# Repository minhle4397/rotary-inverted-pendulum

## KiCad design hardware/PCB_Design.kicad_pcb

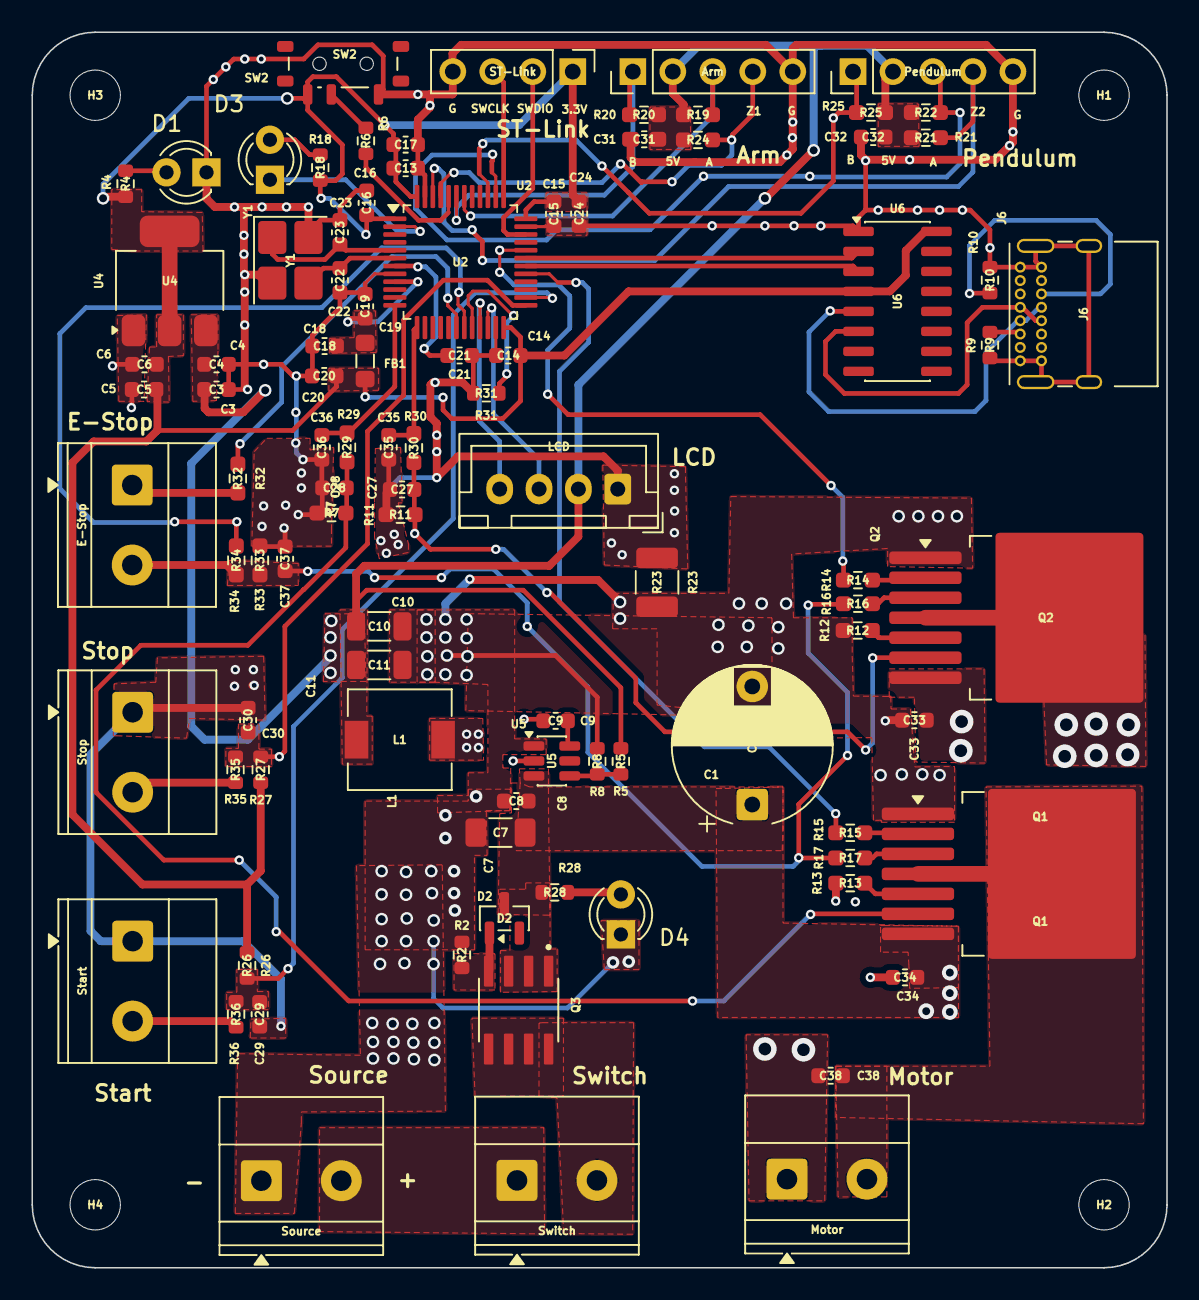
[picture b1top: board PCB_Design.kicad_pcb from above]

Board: 2 copper layers, 72.1 x 78.5 mm, 98 parts (0 on the bottom side), 60 nets.

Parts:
Arm: Encoder_Arm; PinHeader_1x05_P2.54mm_Vertical
C1: C_Radial 10x7.5 1000uF/25V; CP_Radial_D10.0mm_P7.50mm
C3, C5: 10uF 0603/10V; C_0603_1608Metric
C4, C6, C8, C9, C13, C14, C15, C16, C21, C24, C29, C30, C32, C37: 100nF 0603; C_0603_1608Metric
C7: 10uF 1206/25V; C_1206_3216Metric_Pad1.33x1.80mm_HandSolder
C10, C11: 22uF/25v; C_1206_3216Metric
C17: 10uF 0603; C_0603_1608Metric
C18, C35, C36: 10nF 0603; C_0603_1608Metric
C19, C20: 1uF 0603; C_0603_1608Metric
C22, C23: 10pF 0603; C_0603_1608Metric
C27, C28: 1nF 0603; C_0603_1608Metric
C31: 100nF 0603; C_0603_1608Metric_Pad1.08x0.95mm_HandSolder
C33, C34, C38: 100nF 0603 50V; C_0603_1608Metric
D1, D3: LED_Green; LED_D3.0mm
D2: BZX84C12; SOT-23
D4: LED_Yellow; LED_D3.0mm
E-Stop: E-Stop; TerminalBlock_Phoenix_MKDS-1,5-2-5.08_1x02_P5.08mm_Horizont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
FB1: 120R 0805; L_0805_2012Metric_Pad1.05x1.20mm_HandSolder
H1, H2, H3, H4: MountingHole; MountingHole_3.2mm_M3
J6: USB_C_Receptacle_USB2.0_16P; USB_C_Receptacle_GCT_USB4085
L1: 15uH; L_6.3x6.3_H3
LCD: LCD; JST_XH_B4B-XH-A_1x04_P2.50mm_Vertical
Motor: Motor; TerminalBlock_Phoenix_MKDS-1,5-2-5.08_1x02_P5.08mm_Horizont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
Pendulum: Encoder_Pendulum; PinHeader_1x05_P2.54mm_Vertical
Q1, Q2: BTN8982TA; TO-263-7_TabPin8
Q3: AO4407A; SOIC127P600X175-8N
R2, R5: 100k/0603; R_0603_1608Metric
R4: 4.7k/0603; R_0603_1608Metric
R6, R26, R27, R31: 10k 0603; R_0603_1608Metric
R7, R11: 3.3k 0603; R_0603_1608Metric_Pad0.98x0.95mm_HandSolder
R8: 13.3k/0603; R_0603_1608Metric
R9, R10: 5.1k 0603; R_0603_1608Metric
R12, R13, R14, R15, R16, R17, R32: 1k 0603; R_0603_1608Metric_Pad0.98x0.95mm_HandSolder
R18: 1k/0603; R_0603_1608Metric
R19, R20, R21, R22, R24, R25, R29, R30: 4.7k 0603; R_0603_1608Metric_Pad0.98x0.95mm_HandSolder
R23: 0R 1210; R_1210_3225Metric_Pad1.30x2.65mm_HandSolder
R28: 10k/0603; R_0603_1608Metric
R33, R34: 10k 0603; R_0603_1608Metric_Pad0.98x0.95mm_HandSolder
R35, R36: 100R 0603; R_0603_1608Metric
ST-Link: ST-LINK; PinHeader_1x04_P2.54mm_Vertical
SW2: MSK-12C02; SW_SPDT_Shouhan_MSK12C02
Source: Domino 1x2; TerminalBlock_Phoenix_MKDS-1,5-2-5.08_1x02_P5.08mm_Horizont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
Start: Start Button; TerminalBlock_Phoenix_MKDS-1,5-2-5.08_1x02_P5.08mm_Horizont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
Stop: Stop Button; TerminalBlock_Phoenix_MKDS-1,5-2-5.08_1x02_P5.08mm_Horizont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
Switch: Switch; TerminalBlock_Phoenix_MKDS-1,5-2-5.08_1x02_P5.08mm_Horizont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
U2: STM32F103C8T6; LQFP-48_7x7mm_P0.5mm
U4: AMS1117-3.3; SOT-223-3_TabPin2
U5: TPS54202DDC; SOT-23-6
U6: CH340C; SOIC-16_3.9x9.9mm_P1.27mm
Y1: 16MHz; Crystal_SMD_3225-4Pin_3.2x2.5mm_HandSoldering

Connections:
3.3V: C5.1, C6.1, C13.1, C14.1, C15.1, C16.1, C17.1, C20.1, C24.2, FB1.2, R4.1, R18.2, R26.1, R27.1, ST-Link.1, SW2.3 (C), U2.1 (VBAT), U2.24 (VDD), U2.36 (VDD), U2.48 (VDD), U4.2 (VO), U6.4 (V3), U6.16 (VCC)
5V: Arm.2, C3.1, C4.1, C10.1, C11.1, C31.1, C32.1, L1.2, LCD.2, Pendulum.2, R5.1, R19.1, R20.2, R21.2, R22.1, R24.1, R25.2, U4.3 (VI)
+3.3VA: C18.1, C19.1, FB1.1, U2.9 (VDDA)
/MCU/BOOT0: R6.2, U2.44 (BOOT0)
/MCU/HSE_In: C23.1, U2.5 (PD0), Y1.1
/MCU/HSE_Out: C22.1, U2.6 (PD1), Y1.3
/MCU/NRST: C21.1, U2.7 (NRST)
/MCU/PC13: D3.1 (K), U2.2 (PC13)
/MCU/RX: U2.31 (PA10), U6.2 (TXD)
/MCU/SWCLK: ST-Link.3, U2.37 (PA14)
/MCU/SWDIO: ST-Link.2, U2.34 (PA13)
/MCU/SW_BOOT0: R6.1, SW2.2 (B)
/MCU/TX: U2.30 (PA9), U6.3 (RXD)
GND: Arm.5, C3.2, C4.2, C5.2, C6.2, C13.2, C14.2, C15.2, C16.2, C17.2, C18.2, C19.2, C20.2, C21.2, C22.2, C23.2, C24.1, C27.2, C28.2, C29.2, C30.2, C31.2, C32.2, C35.1, C36.1, C37.2, D1.1 (K), J6.A1 (GND), J6.A12 (GND), J6.B1 (GND), J6.B12 (GND), J6.SH (SHIELD), LCD.1, Pendulum.5, R7.2, R9.2, R10.2, R11.2, R23.1, R31.1, R33.2, ST-Link.4, SW2.1 (A), Start.1, Stop.1, U2.8 (VSSA), U2.23 (VSS), U2.35 (VSS), U2.47 (VSS), U4.1 (GND), U6.1 (GND), Y1.2 (G), Y1.4 (G)
GNDPWR: C1.2, C7.2, C8.2, C10.2, C11.2, C33.2, C34.2, D4.1 (K), Q1.1, Q2.1, R2.1, R8.2, R12.1, R13.1, R23.2, Source.1, U5.1 (GND)
INH1: C37.1, E-Stop.2, R16.1, R17.1, R33.1, R34.2
IS1: C36.2, R29.1, U2.12 (PA2)
IS2: C35.2, R30.1, U2.13 (PA3)
unnamed: D1.2 (A), R4.2
unnamed: D2.1 (A), Q3.4, R2.2
unnamed: D3.2 (A), R18.1
unnamed: D4.2 (A), R28.2
unnamed: C38.2, Motor.1, Q2.4, Q2.8
unnamed: C38.1, Motor.2, Q1.4, Q1.8
unnamed: J6.A5 (CC1), R9.1
unnamed: J6.B5 (CC2), R10.1
unnamed: R36.1, Start.2
unnamed: R35.1, Stop.2
unnamed: E-Stop.1, R32.2
unnamed: Source.2, Switch.1
unnamed: Q3.5, Q3.6, Q3.7, Q3.8, Switch.2
unnamed: Q1.2 (IN), R15.1
unnamed: Q1.3 (INH), R17.2
unnamed: C28.1, Q1.6 (IS), R7.1, R29.2
unnamed: Q1.5 (SR), R13.2
unnamed: Q2.2 (IN), R14.1
unnamed: Q2.3 (INH), R16.2
unnamed: C27.1, Q2.6 (IS), R11.1, R30.2
unnamed: Q2.5 (SR), R12.2
unnamed: R31.2, U2.20 (PB2)
unnamed: C9.1, U5.6 (BOOT)
unnamed: R5.2, R8.1, U5.4 (FB)
unnamed: C9.2, L1.1, U5.2 (SW)
unnamed: J6.A6 (D+), J6.B6 (D+), U6.5 (UD+)
unnamed: J6.A7 (D-), J6.B7 (D-), U6.6 (UD-)
PA8: R15.2, U2.29 (PA8)
PA11: R14.2, U2.32 (PA11)
PA15: Pendulum.3, R22.2, U2.38 (PA15)
PB0: R32.1, U2.18 (PB0)
PB1: R34.1, U2.19 (PB1)
PB3: Pendulum.1, R25.1, U2.39 (PB3)
PB6: Arm.3, R19.2, U2.42 (PB6)
PB7: Arm.1, R20.1, U2.43 (PB7)
PB10: LCD.4, U2.21 (PB10)
PB11: LCD.3, U2.22 (PB11)
PB12: C30.1, R27.2, R35.2, U2.25 (PB12)
PB13: C29.1, R26.2, R36.2, U2.26 (PB13)
Phase Z1: Arm.4, R24.2, U2.45 (PB8)
Phase Z2: Pendulum.4, R21.1, U2.46 (PB9)
input: C1.1, C7.1, C8.1, C33.1, C34.1, D2.3 (K), Q1.7, Q2.7, Q3.1, Q3.2, Q3.3, R28.1, U5.3 (VIN)

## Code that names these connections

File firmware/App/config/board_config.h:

/**
 * @file board_config.h
 * @brief Board-level constants of the RIP controller PCB
 * Everything that depends on the WIRING (directions, sense resistors, I2C
 * address) lives here.
 * Pin assignment is done in STM32CubeMX and reaches the code
 * only through the CubeMX user labels used in bsp_stm32f1.c.
 */

#ifndef BOARD_CONFIG_H
#define BOARD_CONFIG_H

#define FW_VERSION_STR "1.0.0"

/** encoder
 * AMT102-V, DIP switch set to 2048 P/R -> 8192 counts/rev in x4 mode.
 * Note: on the PCB channel A of both encoders goes to timer CH2 (PB7, PB3),
 * so the hardware count direction is probably inverted -> [VERIFY].
 */
#define BOARD_ENC_ARM_DIR  (+1) // VERIFY +1 or -1
#define BOARD_ENC_PEND_DIR (+1) // VERIFY +1 or -1

/** power stage
 * 2 x BTN8982TA, sign-magnitude PWM 20 kHz (TIM1 CH1 = PA8 half-bridge A,
 * TIM1 CH4 = PA11 half-bridge B). Positive voltage must give positive dtheta.
 */
#define BOARD_MOTOR_DIR      (+1) // VERIFY +1 or -1
#define BOARD_VBUS_NOMINAL_V (12.0f)

/** current sense
 * I_load = V_IS / R_IS * kILIS -> 4.76 mA/LSB
 */
#define BOARD_IS_R_OHM             (3300.0f)  // 3k3 ohms
#define BOARD_IS_KILIS             (19500.0f) //[VERIFY] calibrate, datasheet 14000..25000
#define BOARD_ADC_VREF_V           (3.3f)     // 3.3V reference for ADC
#define BOARD_ADC_FULL_SCALE       (4095.0f)  // 12-bit ADC
#define BOARD_IS_FAULT_RAW         (3900u)    // BTN8982TA FAULT current saturates the ADC
#define BOARD_IS_SWAP              (0)        // [VERIFY] 1 if IS1 (PA2) belongs to half-bridge B
#define BOARD_IS_MIN_DUTY          (0.10f)    // below this the IS sample is not trusted
#define BOARD_ADC_SAMPLES_PER_TICK (20u)      // 20kHz PWM/ 1kHz control
#define BOARD_ADC_TRIG_MIN_CNT     (72u)      // >= 1 us after the PWM rising edge

/** hmi
 */
#define BOARD_LCD_I2C_ADDR         (0x27u) // PCF8574 backpack: 0x27 or 0x3F [VERIFY]
#define BOARD_BTN_DEBOUNCE_SAMPLES (3u)    // x10ms

/** application
 */
#define APP_START_WINDOW_DEG (10.0f) // START only if |theta| < this
#define APP_ARMING_TICKS     (10u)   // 10 ms bridge enable before E-stop check

/** safety
 * Arm limit 45 deg comes from rip_params_autogen.h (RIP_S_THETA_TRIP)
 */
#define SAFETY_I_TRIP_A     (3.5f)  // < stall current 3.8 A
#define SAFETY_I_TRIP_TICKS (50u)   // 50 ms above the limit
#define SAFETY_DTHETA_MAX   (15.0f) // rad/s, design max 5.35 rad/s
#define SAFETY_DALPHA_MAX   (60.0f) // rad/s, design max 12.9 rad/s
#define SAFETY_EXEC_MAX_US  (800u)  // control tick budget 1000 us

/** telemetry
 */
#define TLM_DEFAULT_DECIMATION (1u) // 1 = every tick (1kHz, ~44 kB/s)

#endif

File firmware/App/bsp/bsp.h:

/**
 * @file bsp.h
 * @brief Board support package interface - the only boundary to hardware
 * Implementation
 * bsp_stm32f1.c        target, built on the STM32CubeMX generated HAL handles
 * host/sil/bsp_sim.c   software-in-the-loop: the same firmware runs on a PC
 *                      against a nonlinear plant model
 * host/tests/bsp_fake.c unit tests
 * Everything above this layer (drivers, services, control, app) is portable C
 * and never includes a HAL header.
 */

#ifndef BSP_H
#define BSP_H

#include <stdbool.h>
#include <stdint.h>

typedef void (*bsp_tick_cb_t)(void);

// lifecycle
// Start encoders, PWM, ADC+DMA and UART RX. Bridge stays DISABLED
void bsp_init(void);
// Start the 1kHz control interrupt (TIM3) and call cb from it.
void bsp_tick_start(bsp_tick_cb_t cb);

// sensors
uint16_t bsp_enc_arm_raw(void);  // TIM4 counter (theta)
uint16_t bsp_enc_pend_raw(void); // TIM2 counter (alpha)
// Mean of the IS1/IS2 ADC samples taken since the previous call [LSB]
void bsp_current_raw(uint16_t *is_a, uint16_t *is_b);

// power stage
uint16_t bsp_pwm_period(void); //< ARR + 1 (3600 @ 20 kHz)
// Compare values of half-bridge A (PA8) and B (PA11); period = 100%
void bsp_pwm_set(uint16_t cmp_a, uint16_t cmp_b);
// ADC trigger instant inside the PWM period (TIM1 CH3 compare)
void bsp_adc_trigger_set(uint16_t cmp);
// BTN8982 INH through the E-stop chain (PB0)
void bsp_bridge_enable(bool enable);
// Reads the INH node (PB1): true = bridge enabled AND E-stop closed
bool bsp_bridge_inhibit_sense(void);

// HMI
bool bsp_btn_start_raw(void); // true = pressed (active low on PCB)
bool bsp_btn_stop_raw(void);
void bsp_led_set(bool on);
bool bsp_i2c_write(uint8_t addr7, const uint8_t *buf, uint16_t len);

// Non-blocking DMA transmit. buf must stay valid until bsp_uart_tx_busy() is false
bool bsp_uart_tx(const uint8_t *buf, uint16_t len);
bool bsp_uart_tx_busy(void);
// Copy received bytes (circular DMA) into buf, returns the count
uint16_t bsp_uart_rx(uint8_t *buf, uint16_t max);

// time
uint32_t bsp_millis(void);
void     bsp_delay_ms(uint32_t ms);
uint32_t bsp_cycles(void); //<dwt cycle counter
uint32_t bsp_cycles_per_us(void);

// system
void     bsp_watchdog_kick(void);
uint32_t bsp_irq_lock(void);
void     bsp_irq_unlock(uint32_t key);

#endif
